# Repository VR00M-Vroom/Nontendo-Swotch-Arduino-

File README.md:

# Why?
The first thing I saw when I joined hackclub was Sprig! this low power Pi based handheld console that was very simple to us, modify and upolad games to, so based on this I wanted to create my own. This led to me creating the Nontendo Swotch, its a handheld thats very easy to build requires a few parts and is based on a unanimous microcontroller the arduino. The games are coded via C++ adn the Arduino IDE.

 # CAD 

 # PCB 

 # Schematic 

 ## Bill of Materials 

Display - 1x
-
https://www.amazon.com/Haldzemo-Display-Module-Compatible-Arduino/dp/B0FC2B4J1R?sr=1-6

Tactile switches - 8x
-
https://www.amazon.com/Hilitchi-200-Pcs-Tactile-Momentary-Assortment/dp/B071YPZ4G1?sr=8-3

Battery - 1x
-
https://www.amazon.com/OXWINOU-402030-Rechargeable-Replacement-Electronic/dp/B0CKWZH5M4?sr=8-2

Arduino nano - 1x
-
https://www.amazon.com/LUIRSAY-2Pcs-ATmega328P-Microcontroller-Compatible/dp/B0F1FQMNXM?sr=8-4

Slide Switch - 1x
-
https://www.amazon.com/HiLetgo-SS-12D00-Toggle-Switch-Vertical/dp/B07RTJDW27?sr=8-5

Buzzers - 2x 
-
https://www.amazon.com/3V-Active-Buzzer-Continous-Raspberry/dp/B0FN7FHYQM?sr=8-5\

JST Connectors - 1x
-
https://www.amazon.com/JST-PH-Connector-Silicone-Cables-Female/dp/B0D7Q9HJLQ?sr=1-10

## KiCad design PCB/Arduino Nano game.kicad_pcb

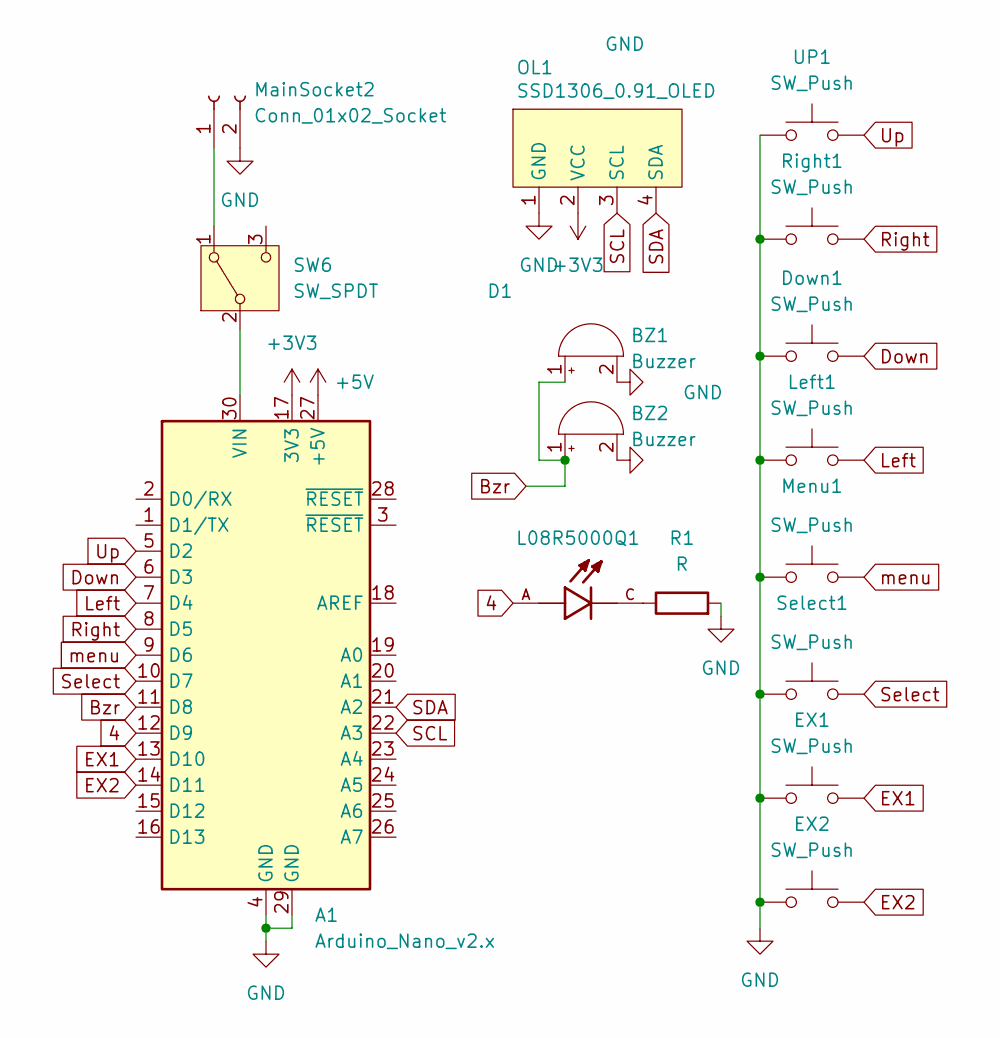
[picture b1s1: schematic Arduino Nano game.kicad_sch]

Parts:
A1: Arduino_Nano_v2.x; Arduino_Nano
BZ1, BZ2: Buzzer; Buzzer_12x9.5RM7.6
D1: L08R5000Q1; LEDRD254W57D500H1070; PARTREV NA
Down1: SW_Push; SW_PUSH-12mm_Wuerth-430476085716
EX1, EX2: SW_Push; SW_PUSH-12mm_Wuerth-430476085716
Left1: SW_Push; SW_PUSH-12mm_Wuerth-430476085716
MainSocket2: Conn_01x02_Socket; PinSocket_1x02_P2.54mm_Vertical
Menu1: SW_Push; SW_PUSH-12mm_Wuerth-430476085716
OL1: SSD1306_0.91_OLED; SSD1306-0.91-OLED-4pin-128x32
R1: R; R_Axial_DIN0204_L3.6mm_D1.6mm_P7.62mm_Horizontal
Right1: SW_Push; SW_PUSH-12mm_Wuerth-430476085716
SW6: SW_SPDT; SW_Slide-03_Wuerth-WS-SLTV_10x2.5x6.4_P2.54mm
Select1: SW_Push; SW_PUSH-12mm_Wuerth-430476085716
UP1: SW_Push; SW_PUSH-12mm_Wuerth-430476085716

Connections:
4: A1.12 (D9), D1.A
+3V3: A1.17 (3V3), OL1.2 (VCC)
+5V: A1.27 (+5V)
Bzr: A1.11 (D8), BZ1.1 (+), BZ2.1 (+)
Down: A1.6 (D3), Down1.2
EX1: A1.13 (D10), EX1.2
EX2: A1.14 (D11), EX2.2
GND: A1.4 (GND), A1.29 (GND), BZ1.2 (-), BZ2.2 (-), Down1.1, EX1.1, EX2.1, Left1.1, MainSocket2.2, Menu1.1, OL1.1 (GND), R1.2, Right1.1, Select1.1, UP1.1
Left: A1.7 (D4), Left1.2
unnamed: A1.30 (VIN), SW6.2 (B)
unnamed: D1.C, R1.1
unnamed: MainSocket2.1, SW6.1 (A)
Right: A1.8 (D5), Right1.2
SCL: A1.22 (A3), OL1.3 (SCL)
SDA: A1.21 (A2), OL1.4 (SDA)
Select: A1.10 (D7), Select1.2
Up: A1.5 (D2), UP1.2
menu: A1.9 (D6), Menu1.2

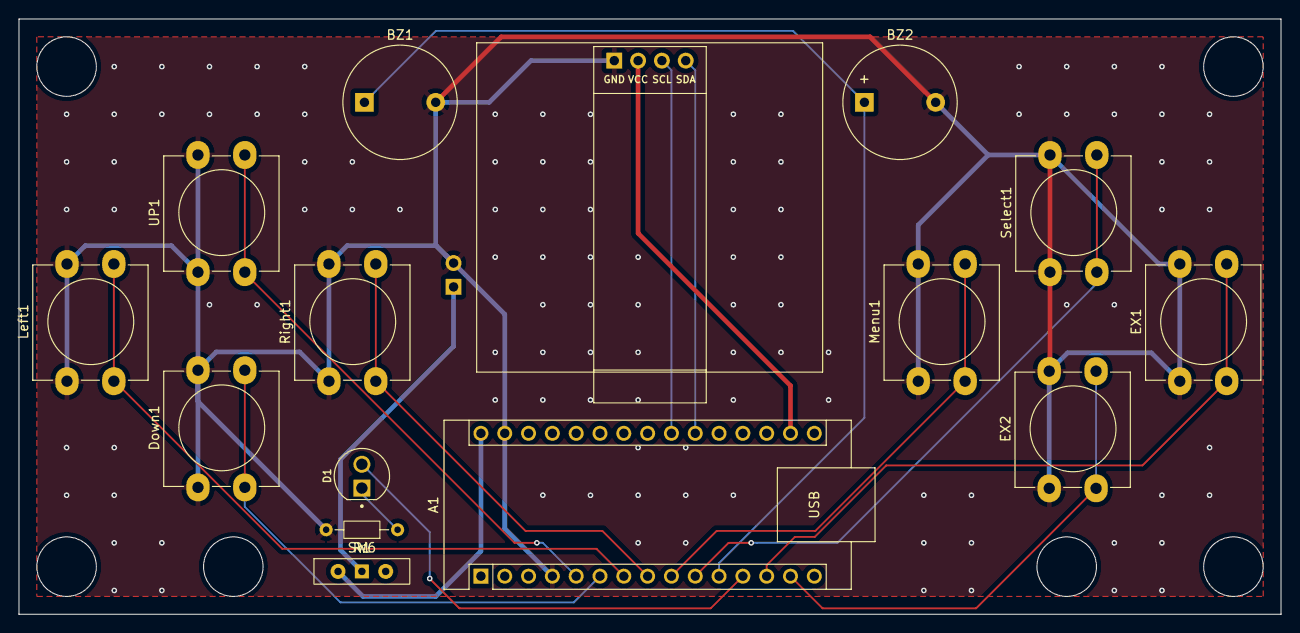
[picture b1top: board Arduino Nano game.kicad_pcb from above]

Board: 2 copper layers, 134.6 x 63.5 mm, 16 parts (1 on the bottom side), 17 nets.

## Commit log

2025-12-29 Create a
2025-12-29 Revise README with improved formatting and BOM
    Updated formatting and added new components with links.
2025-12-29 Update links for buzzers and add JST connectors
    Added links for JST connectors and updated buzzer link.
